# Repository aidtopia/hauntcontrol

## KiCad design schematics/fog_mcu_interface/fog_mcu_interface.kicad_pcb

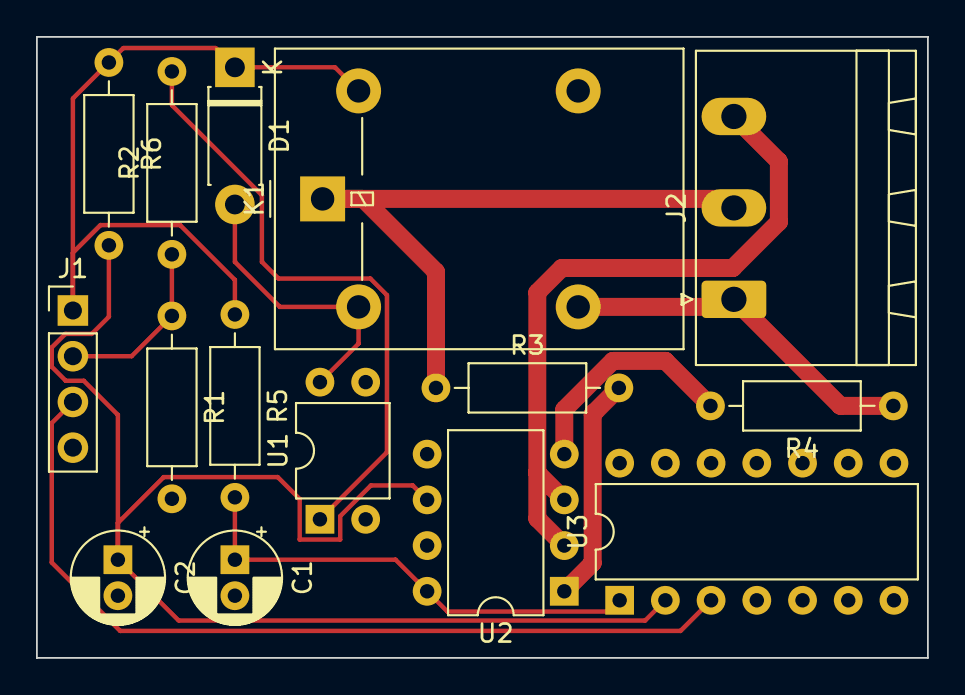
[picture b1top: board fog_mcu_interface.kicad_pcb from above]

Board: 2 copper layers, 49.5 x 34.5 mm, 15 parts (0 on the bottom side), 13 nets.

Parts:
C1, C2: 1uF; CP_Radial_D5.0mm_P2.00mm
D1: 1N4001; D_DO-41_SOD81_P7.62mm_Horizontal
J1: Conn_01x04_Male; PinHeader_1x04_P2.54mm_Vertical
J2: Screw_Terminal_01x03; PhoenixContact_MSTBA_2,5_3-G-5,08_1x03_P5.08mm_Horizontal
K1: G5LE-1; Relay_SPDT_Omron-G5LE-1
R1: 100K; R_Axial_DIN0207_L6.3mm_D2.5mm_P10.16mm_Horizontal
R2: 200; R_Axial_DIN0207_L6.3mm_D2.5mm_P10.16mm_Horizontal
R3, R4: 6K2; R_Axial_DIN0207_L6.3mm_D2.5mm_P10.16mm_Horizontal
R5, R6: 10K; R_Axial_DIN0207_L6.3mm_D2.5mm_P10.16mm_Horizontal
U1: LTV-817; DIP-4_W7.62mm
U2: LTV-824; DIP-8_W7.62mm
U3: 74HC86; DIP-14_W7.62mm

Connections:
+5V: D1.1 (K), J1.1, K1.5, R5.1, R6.1
/FOG: J1.2, R1.1, R2.1
/READY: J1.3, U3.3
/S1: C2.1, R6.2, U2.6, U3.2
/S2: C1.1, R5.2, U2.8, U3.1
GND: C1.2, C2.2, J1.4, R1.2, U1.2, U1.3, U2.5, U2.7
unnamed: D1.2 (A), K1.2, U1.4
unnamed: J2.1, K1.3, R4.1
unnamed: J2.2, K1.1, R3.1
unnamed: J2.3, U2.2, U2.3
unnamed: R2.2, U1.1
unnamed: R3.2, U2.1
unnamed: R4.2, U2.4

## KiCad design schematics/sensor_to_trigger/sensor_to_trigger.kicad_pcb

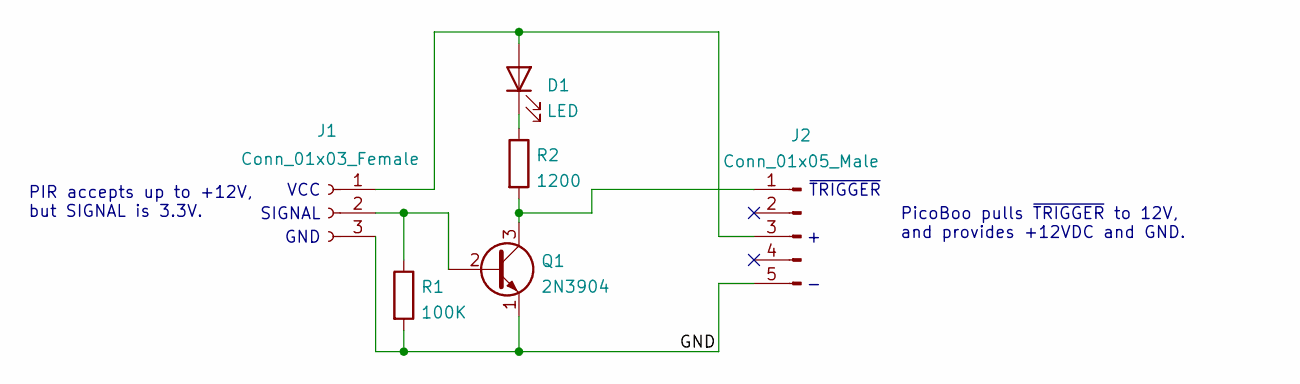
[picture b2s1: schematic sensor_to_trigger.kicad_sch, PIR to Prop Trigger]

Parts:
D1: LED; LED_D5.0mm
J1: Conn_01x03_Female; TerminalBlock_bornier-3_P5.08mm
J2: Conn_01x05_Male; PinHeader_1x05_P2.54mm_Vertical
Q1: 2N3904; TO-92_Inline_Wide
R1: 100K; R_Axial_DIN0207_L6.3mm_D2.5mm_P10.16mm_Horizontal
R2: 1200; R_Axial_DIN0207_L6.3mm_D2.5mm_P10.16mm_Horizontal

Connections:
/GND: J1.3, J2.5, Q1.1 (E), R1.2
unnamed: D1.1 (K), R2.1
unnamed: D1.2 (A), J1.1, J2.3
unnamed: J1.2, Q1.2 (B), R1.1
unnamed: J2.1, Q1.3 (C), R2.2

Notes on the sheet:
SIGNAL
PicoBoo pulls ~{TRIGGER} to 12V, and provides +12VDC and GND.
~{TRIGGER}
GND
VCC
PIR accepts up to +12V, but SIGNAL is 3.3V.

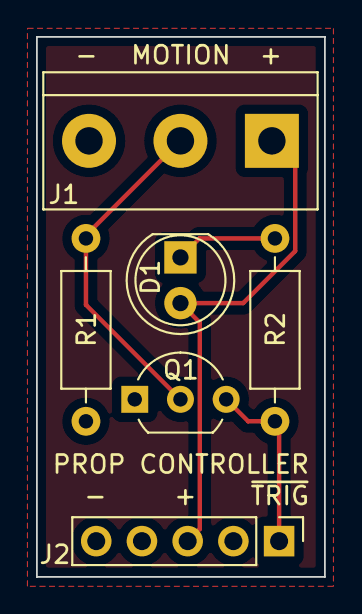
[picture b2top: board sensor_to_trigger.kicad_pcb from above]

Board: 2 copper layers, 16.0 x 30.0 mm, 6 parts (0 on the bottom side), 5 nets.

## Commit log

2021-03-30 Moving project into source control
2021-03-30 Bring the serial audio player documentation into the project.
    This document was originally created in my personal cache of datasheets.
    Moving it adjacent to the code makes more sense and is more convenient
    for source control.
2021-10-23 Move the experimental msgeq07 code out to its own header.
2021-10-25 Added basic motion sensor functionality.
2021-10-31 Quick hack for motion-sensing spitter.
2021-10-31 Moved the parser hack out of the main sketch.
2021-10-31 Moved command buffer management into a class.
2021-12-18 Added lcd_display.h. Refactored AudioModule to simplify connecting to different serial devices.
2021-12-18 Added bracket to hold multiple motion sensors for side-by-side testing.
2021-12-18 Changed serial interface pointer to a reference for consistency.
2021-12-18 Added beginning of laser vortex.
    So far, this just sets up Timer2 to modulate the laser output.
2021-12-19 Switched back to Arduino Pro Mini for now.
    I found the breadboard setup and realized it was further along than
    I remembered.
2021-12-20 Restored LED display of EQ channel that best detects thunder. Added EQ settings to the parser. Fixed typos.
2021-12-23 Added a class for rotary encoders. It's not yet complete.
2021-12-24 Fixed some rotary encoder bugs. Freed up underutilized pins.
2021-12-29 Re-enabled the LCD display.
2022-01-01 Made the AudioModule less chatty.
2022-01-01 Tried to templatize Format, bug was blocked by a gcc bug.
    The template compiles fine in Compiler Explorer (godbolt.org) set for
    Arduino, but CE uses Arduino 1.8.9 and I have 1.8.13, so apparently
    the bug is in the newer compiler.
    So Format isn't templatized, but there are some inconsequential changes
    from the previous commit.
2023-09-12 Added a simplistic fogger control. Fixed some audio state bugs.
2023-09-12 Added refernce schematics for a fog machine and some remotes and timers.
2023-09-12 Added a .gitignore to keep the schematics tidy.
2023-10-02 Triple checking how the basic wired remotes work with fog machines.
2023-10-10 Added schematic for my Fogger Tester.
    This circuit demonstrates the differences between the remote socket pin
    assignments for the two styles of "party-store" fog machines.
2023-10-10 Added coffin_knocker.
    WIP for a new controller for the Coffin Knocker prop Ralph & Gigi have.
    Original controller wasn't working well anymore, and it ran off a
    whopping nine batteries!
2023-10-12 Coffin Knocker updates.
2023-10-13 Added .gitignore for Coffin Knocker
2023-10-18 Added a housing for mini PIR sensors.
2023-10-18 Checkpoint after more churn on the Coffin Knocker sketch than I intended.
2023-10-18 Simplified coffin knocker state machine.
2023-10-18 Reworked parameter handling in coffin knocker.
2023-10-19 Uncommented the caps for the mini PIR sensor housing.
2023-10-20 Lots of refactoring and small improvements and needed a checkpoint.
2023-10-20 Refactored parameters and fixed some parsing bugs in Coffin Knocker.
2023-10-21 Fixed some typos.
2023-10-21 Abandoned PIR connection through lid. Now cable does end exit.
2023-11-09 Changed to use a cable gland for strain relief.
    After several failed experiments to print a built-in strain relief, I
    purchased some inexpensive PG7 cable glands and designed the housing
    to allow it to be screwed into the bottom.
    It now uses my new aidthreads library from PrintableParts repot.
2023-11-10 Shortened the PIR housing again.
    The cable gland grips the cable at the end, so the housing doesn't need
    to be as long.
2023-11-18 Designed circuit to interface PIR output to prop controller trigger.
    Essentially, it's a transistor that can be activated by the very low
    current signal from the mini PIR sensor to pull down the trigger on
    a prop controller like a PicoBoo.
2023-11-18 Updated .gitignore.
2023-11-26 Improved notes on PIR-to-trigger schematic.
2024-01-10 [PIR] Added a longer snoot for narrower detection cone.
2024-01-12 [PIR] Made a "snoot" (a cap with a small aperture).
    Just increasing the lengths of the caps wasn't very helpful in limiting
    the width of the detection area. Instead, a cap that has an aperature
    of 3mm (which is approximately the diameter of the central facet in the
    fresnel lens array) does wonders.
2024-01-14 [PIR] More tweaks to the file in preparation for release.
2024-01-14 Moved PIR stuff out of coffin knocker.
2024-04-06 Added wiring diagram for Coffin Knocker Controller.
2024-04-06 Removed second sensor for pir_vs_pir sketch.
2024-04-19 Scrimped a few bytes of RAM and flash, mostly as an experiment.
    Bytes before->after:
    RAM used by globals: 282-> 279
    Flash (progmem): 8394->8222
2024-04-19 Added .gitignore file.
2024-04-19 Checkpoint of idea for making microcontroller interface for fogger.
2024-05-18 [RAVEN] Started hacking together some animation for the raven.
    Specifically Mr. Chicken's Raven kit (by Jasper Anderson), using a
    Pololu Maestro Micro (as a PWM generator for the servos), and an
    Arduino Mega 2560.
    Includes some size tests for 3D printing a handheld controller.
2024-05-24 Some fixes to the serial audio players documentation.
    This is still very much a draft.
2024-05-24 [RAVEN] Got the SMPTE LTC reader working.
    This is still an experimental mess. Time to start organizing and
    improving the code.
2025-09-29 Added defaults to switches to satisfy the compiler.
